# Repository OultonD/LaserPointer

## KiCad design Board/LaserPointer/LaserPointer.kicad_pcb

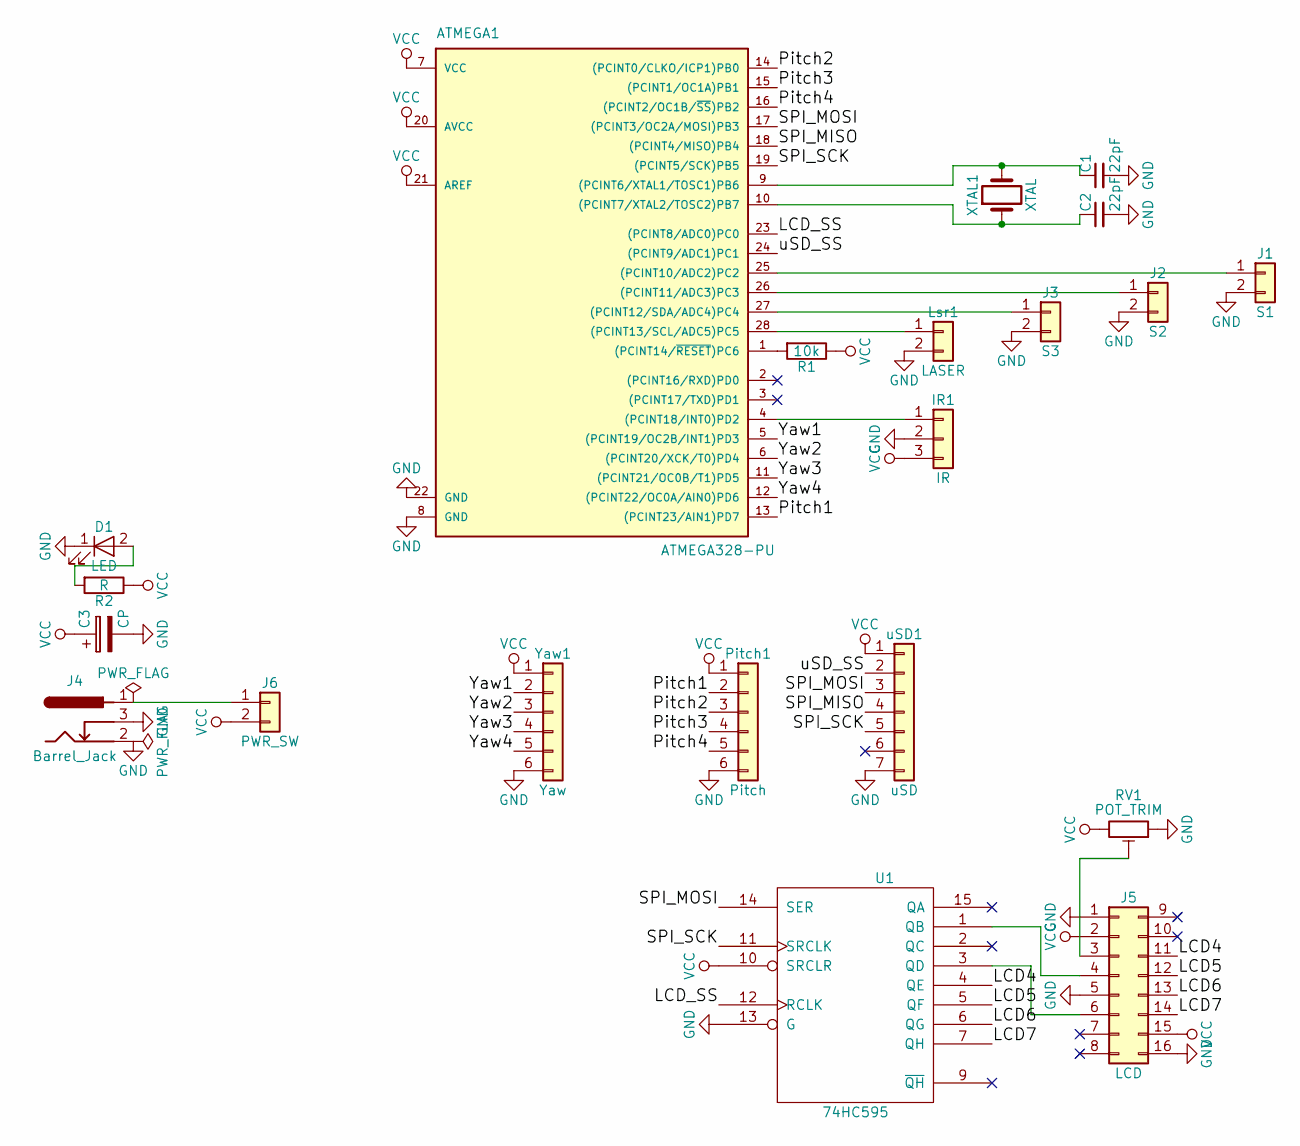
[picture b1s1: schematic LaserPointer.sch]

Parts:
ATMEGA1: ATMEGA328-PU; DIP-28_W7.62mm
C1, C2: 22pF; C_0603_HandSoldering
C3: CP; CP_Radial_D5.0mm_P2.00mm
D1: LED; LED_0603_HandSoldering
IR1: IR; Pin_Header_Straight_1x03_Pitch2.54mm
J1: S1; Pin_Header_Straight_1x02_Pitch2.54mm
J2: S2; Pin_Header_Straight_1x02_Pitch2.54mm
J3: S3; Pin_Header_Straight_1x02_Pitch2.54mm
J4: Barrel_Jack; BARREL_JACK
J5: LCD; Pin_Header_Straight_2x08_Pitch2.54mm
J6: PWR_SW; Pin_Header_Straight_1x02_Pitch2.54mm
Lsr1: LASER; Pin_Header_Straight_1x02_Pitch2.54mm
Pitch1: Pitch; Pin_Header_Straight_1x06_Pitch2.54mm
R1: 10k; R_0603_HandSoldering
R2: R; R_0603_HandSoldering
RV1: POT_TRIM; Potentiometer_Trimmer_Piher_PT-10h2.5_Vertical_Px2.5mm_Py5.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
U1: 74HC595; DIP-16_W7.62mm
XTAL1: XTAL; Crystal_HC49-U_Vertical
Yaw1: Yaw; Pin_Header_Straight_1x06_Pitch2.54mm
uSD1: uSD; Pin_Header_Straight_1x07_Pitch2.54mm

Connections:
/LCD4: J5.11, U1.4 (QE)
/LCD5: J5.12, U1.5 (QF)
/LCD6: J5.13, U1.6 (QG)
/LCD7: J5.14, U1.7 (QH)
/LCD_SS: ATMEGA1.23 ((PCINT8/ADC0)PC0), U1.12 (RCLK)
/Pitch1: ATMEGA1.13 ((PCINT23/AIN1)PD7), Pitch1.2
/Pitch2: ATMEGA1.14 ((PCINT0/CLKO/ICP1)PB0), Pitch1.3
/Pitch3: ATMEGA1.15 ((PCINT1/OC1A)PB1), Pitch1.4
/Pitch4: ATMEGA1.16 ((PCINT2/OC1B/~SS~)PB2), Pitch1.5
/SPI_MISO: ATMEGA1.18 ((PCINT4/MISO)PB4), uSD1.4
/SPI_MOSI: ATMEGA1.17 ((PCINT3/OC2A/MOSI)PB3), U1.14 (SER), uSD1.3
/SPI_SCK: ATMEGA1.19 ((PCINT5/SCK)PB5), U1.11 (SRCLK), uSD1.5
/Yaw1: ATMEGA1.5 ((PCINT19/OC2B/INT1)PD3), Yaw1.2
/Yaw2: ATMEGA1.6 ((PCINT20/XCK/T0)PD4), Yaw1.3
/Yaw3: ATMEGA1.11 ((PCINT21/OC0B/T1)PD5), Yaw1.4
/Yaw4: ATMEGA1.12 ((PCINT22/OC0A/AIN0)PD6), Yaw1.5
/uSD_SS: ATMEGA1.24 ((PCINT9/ADC1)PC1), uSD1.2
unnamed: ATMEGA1.1 ((PCINT14/~RESET~)PC6), R1.2
unnamed: ATMEGA1.4 ((PCINT18/INT0)PD2), IR1.1
unnamed: ATMEGA1.9 ((PCINT6/XTAL1/TOSC1)PB6), C1.1, XTAL1.2
unnamed: ATMEGA1.10 ((PCINT7/XTAL2/TOSC2)PB7), C2.1, XTAL1.1
unnamed: ATMEGA1.25 ((PCINT10/ADC2)PC2), J1.1
unnamed: ATMEGA1.26 ((PCINT11/ADC3)PC3), J2.1
unnamed: ATMEGA1.27 ((PCINT12/SDA/ADC4)PC4), J3.1
unnamed: ATMEGA1.28 ((PCINT13/SCL/ADC5)PC5), Lsr1.1
unnamed: D1.2 (A), R2.2
unnamed: J4.1, J6.1
unnamed: J5.4, U1.1 (QB)
unnamed: J5.6, U1.3 (QD)

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
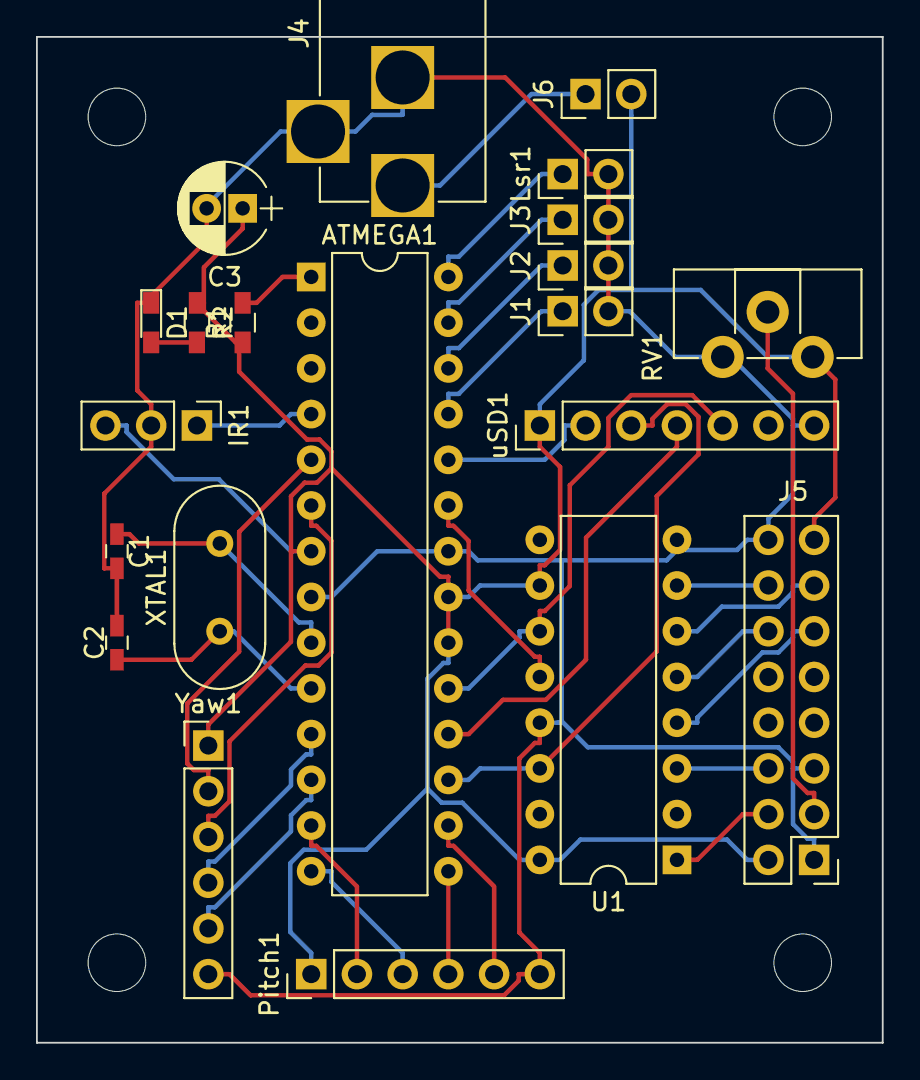
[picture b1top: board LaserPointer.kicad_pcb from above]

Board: 2 copper layers, 47.0 x 55.9 mm, 25 parts (0 on the bottom side), 32 nets.

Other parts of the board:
H1, H2, H3, H4: MountingHole_3.2mm_M3

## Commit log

2018-02-01 init
2018-02-04 Added basic button and laser control
2018-02-07 Initial attempt at LCD, SD, Steppers
2018-02-15 Working stepper code
2018-02-16 Working LCD Code
2018-02-16 Adding IR Remote
2018-02-16 Working SD and Remote code
2018-02-20 Update PCB Files
2018-02-21 Board updates
